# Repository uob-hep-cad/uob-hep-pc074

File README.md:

# Simple Charge Sensitive Amplifier with Integrated Shaping Amplifier

1000 electrons --> 8mV at output of shaper . i.e. ~ 50V/pC

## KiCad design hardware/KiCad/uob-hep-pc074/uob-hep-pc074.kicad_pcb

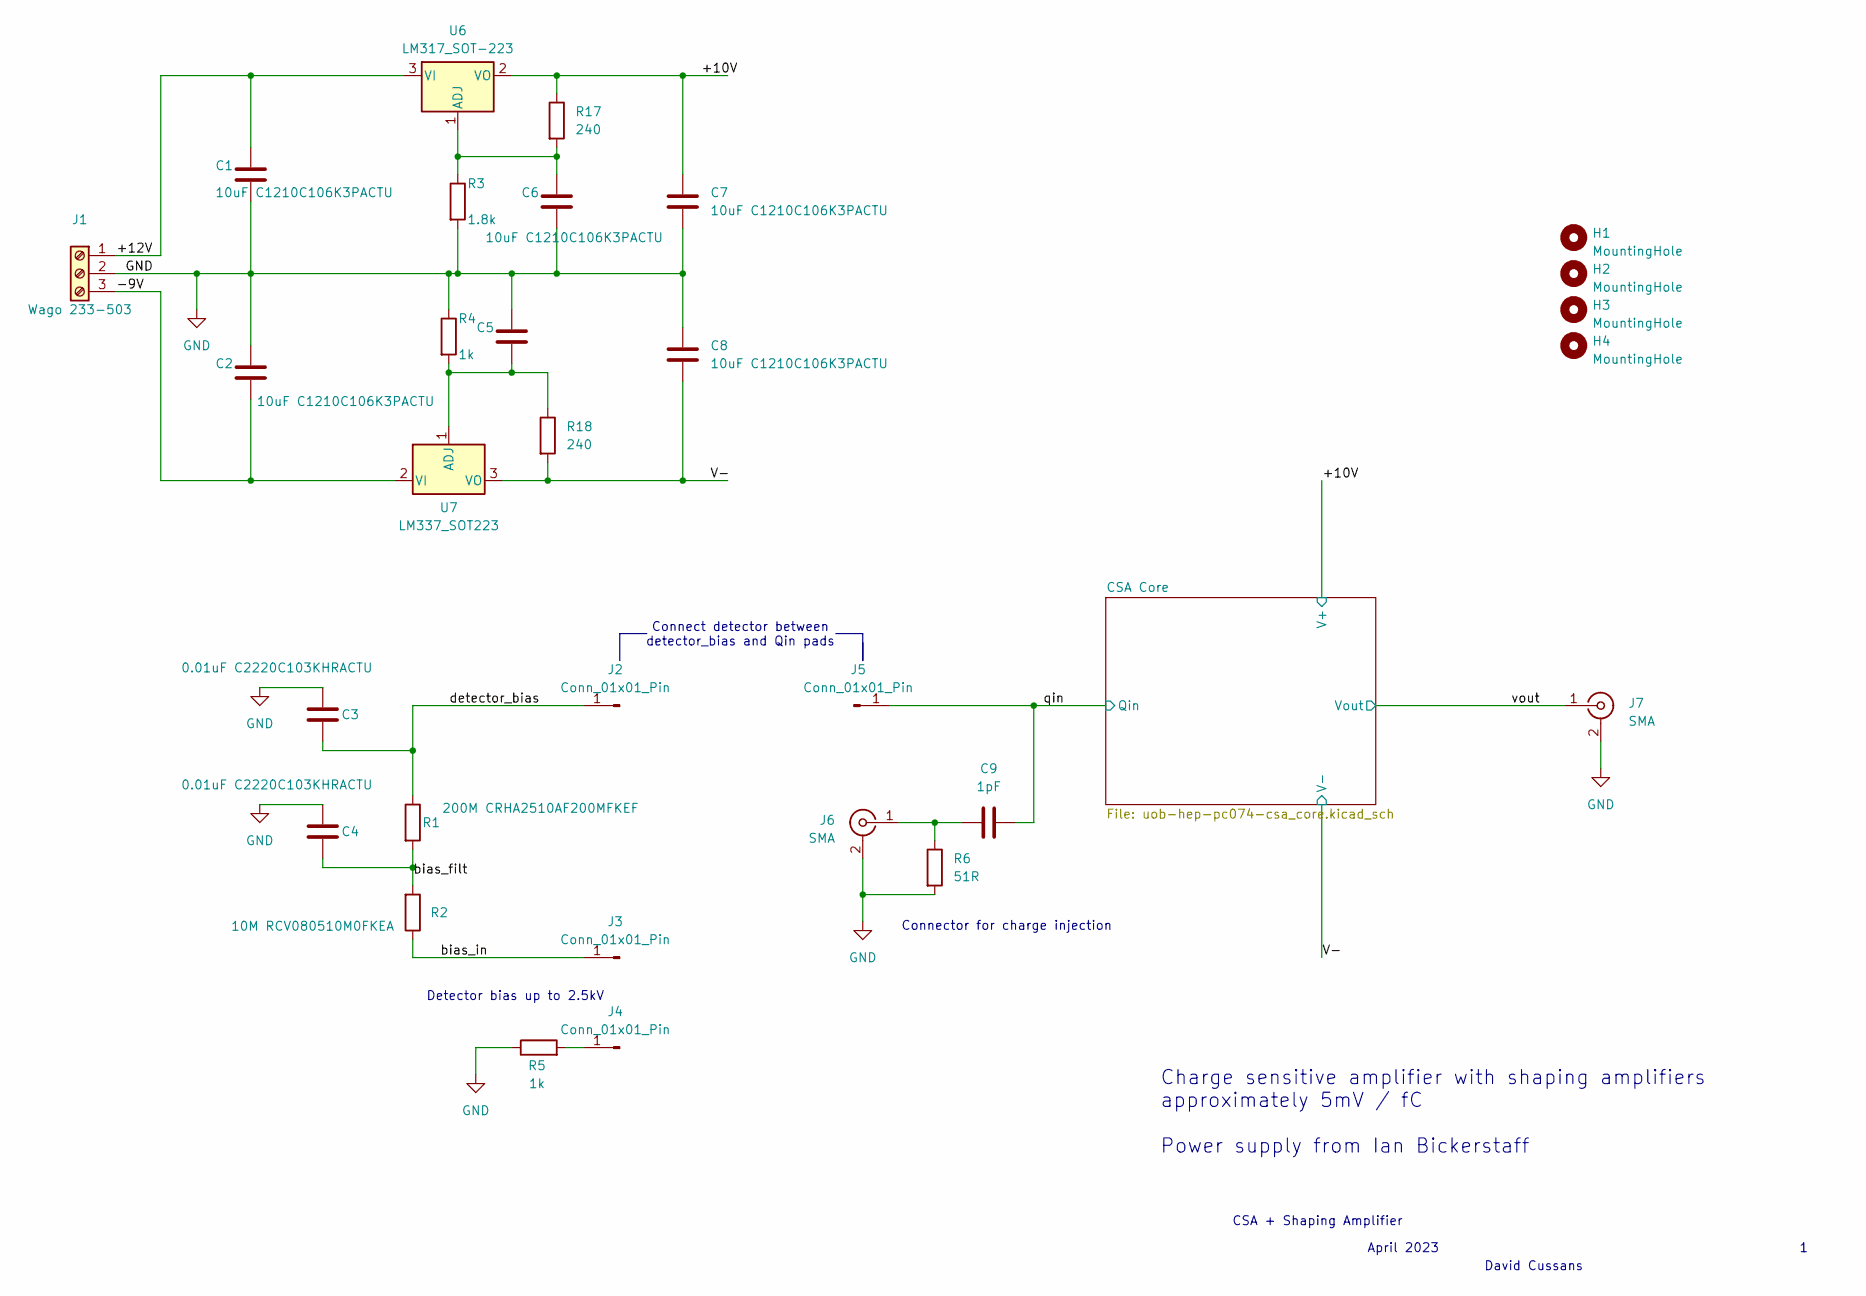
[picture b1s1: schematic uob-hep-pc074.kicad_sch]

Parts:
C1, C2, C5, C6, C7, C8: 10uF C1210C106K3PACTU; C_1210_3225Metric
C3, C4: 0.01uF C2220C103KHRACTU; C_2220_5750Metric_Pad1.97x5.40mm_HandSolder
C9: 1pF; C_0603_1608Metric_Pad1.08x0.95mm_HandSolder
H1, H2, H3, H4: MountingHole; MountingHole_2.7mm_M2.5
J1: Wago 233-503; TerminalBlock_WAGO_233-503_1x03_P2.54mm_45Degree
J2, J3, J4, J5: Conn_01x01_Pin; SolderWire-2sqmm_1x01_D2mm_OD3.9mm
J6, J7: SMA; SMA_Amphenol_901-144_Vertical
R1: 200M CRHA2510AF200MFKEF; R_2512_6332Metric_Pad1.40x3.35mm_HandSolder
R2: 10M RCV080510M0FKEA; R_0805_2012Metric
R3: 1.8k; R_0603_1608Metric_Pad0.98x0.95mm_HandSolder
R4, R5: 1k; R_0603_1608Metric_Pad0.98x0.95mm_HandSolder
R6: 51R; R_0603_1608Metric_Pad0.98x0.95mm_HandSolder
R17, R18: 240; R_0603_1608Metric_Pad0.98x0.95mm_HandSolder
U6: LM317_SOT-223; SOT-223-3_TabPin2
U7: LM337_SOT223; SOT-223-3_TabPin2

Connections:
/+10V: C7.1, R17.1, U6.2 (VO); also elsewhere on the board
/+12V: C1.1, J1.1, U6.3 (VI)
/-9V: C2.2, J1.3, U7.2 (VI)
/V-: C8.2, R18.2, U7.3 (VO); also elsewhere on the board
/bias_filt: C4.1, R1.2, R2.2
/bias_in: J3.1, R2.1
/detector_bias: C3.1, J2.1, R1.1
/qin: C9.2, J5.1; also elsewhere on the board
/vout: J7.1 (In); also elsewhere on the board
GND: C1.2, C2.1, C3.2, C4.2, C5.1, C6.2, C7.2, C8.1, J1.2, J6.2 (Ext), J7.2 (Ext), R3.2, R4.1, R5.1, R6.2; also elsewhere on the board
unnamed: J4.1, R5.2
unnamed: C9.1, J6.1 (In), R6.1
unnamed: C6.1, R3.1, R17.2, U6.1 (ADJ)
unnamed: C5.2, R4.2, R18.1, U7.1 (ADJ)

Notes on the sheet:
CSA + Shaping Amplifier
David Cussans
Connector for charge injection
Detector bias up to 2.5kV
Charge sensitive amplifier with shaping amplifiers approximately 5mV / fC Power supply from Ian Bickerstaff
Connect detector between detector_bias and Qin pads
April 2023

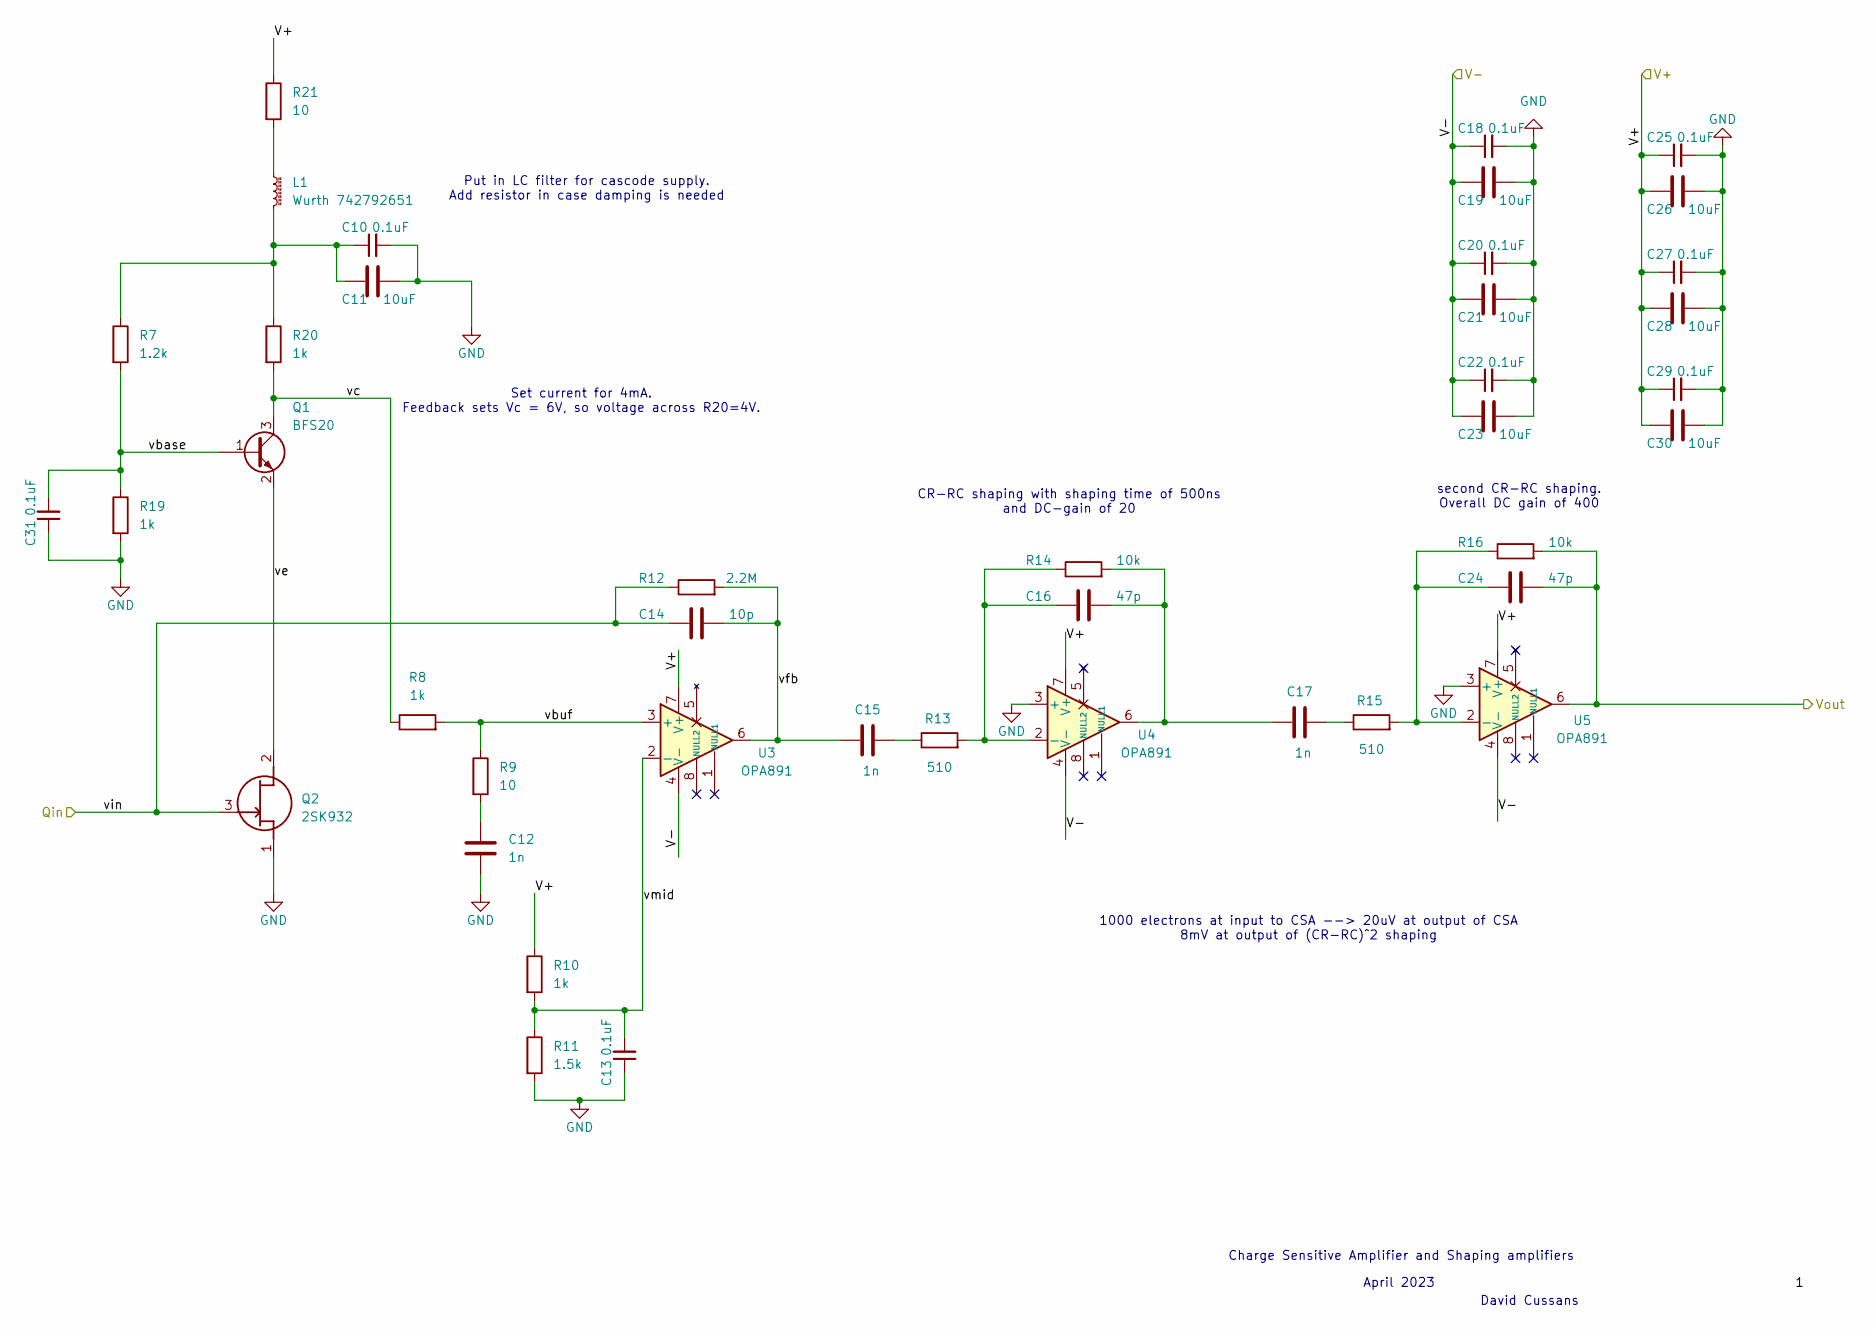
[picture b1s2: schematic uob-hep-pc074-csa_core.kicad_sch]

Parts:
C10, C13, C18, C20, C22, C25, C27, C29, C31: 0.1uF; C_0805_2012Metric
C11, C19, C21, C23, C26, C28, C30: 10uF; C_0805_2012Metric
C12: 1n; C_0603_1608Metric_Pad1.08x0.95mm_HandSolder
C14: 10p; R_0603_1608Metric_Pad0.98x0.95mm_HandSolder
C15, C17: 1n; R_0603_1608Metric_Pad0.98x0.95mm_HandSolder
C16, C24: 47p; R_0603_1608Metric_Pad0.98x0.95mm_HandSolder
L1: Wurth 742792651; L_0603_1608Metric_Pad1.05x0.95mm_HandSolder
Q1: BFS20; SOT-23
Q2: 2SK932; SOT-23; Manufacturer_Part_Number 2SK932
R7: 1.2k; R_0603_1608Metric_Pad0.98x0.95mm_HandSolder
R8, R10, R19, R20: 1k; R_0603_1608Metric_Pad0.98x0.95mm_HandSolder
R9, R21: 10; R_0603_1608Metric_Pad0.98x0.95mm_HandSolder
R11: 1.5k; R_0603_1608Metric_Pad0.98x0.95mm_HandSolder
R12: 2.2M; R_0603_1608Metric_Pad0.98x0.95mm_HandSolder
R13, R15: 510; R_0603_1608Metric_Pad0.98x0.95mm_HandSolder
R14, R16: 10k; R_0603_1608Metric_Pad0.98x0.95mm_HandSolder
U3, U4, U5: OPA891; SOIC-8_5.275x5.275mm_P1.27mm

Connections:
/+10V: C25.1, C26.1, C27.1, C28.1, C29.1, C30.1, R10.1, R21.1, U3.7 (V+), U4.7 (V+), U5.7 (V+); also elsewhere on the board
/CSA Core/vbase: C31.2, Q1.1 (B), R7.2, R19.1
/CSA Core/vbuf: R8.2, R9.1, U3.3 (+)
/CSA Core/vc: Q1.3 (C), R8.1, R20.2
/CSA Core/ve: Q1.2 (E), Q2.2 (D)
/CSA Core/vfb: C14.2, C15.1, R12.2, U3.6
/CSA Core/vmid: C13.2, R10.2, R11.1, U3.2 (-)
/V-: C18.1, C19.1, C20.1, C21.1, C22.1, C23.1, U3.4 (V-), U4.4 (V-), U5.4 (V-); also elsewhere on the board
/qin: C14.1, Q2.3 (G), R12.1; also elsewhere on the board
/vout: C24.2, R16.2, U5.6; also elsewhere on the board
GND: C10.2, C11.2, C12.2, C13.1, C18.2, C19.2, C20.2, C21.2, C22.2, C23.2, C25.2, C26.2, C27.2, C28.2, C29.2, C30.2, C31.1, Q2.1 (S), R11.2, R19.2, U4.3 (+), U5.3 (+); also elsewhere on the board
unnamed: C10.1, C11.1, L1.2, R7.1, R20.1
unnamed: C12.1, R9.2
unnamed: C15.2, R13.1
unnamed: C16.2, C17.1, R14.2, U4.6
unnamed: C17.2, R15.1
unnamed: L1.1, R21.2
unnamed: C16.1, R13.2, R14.1, U4.2 (-)
unnamed: C24.1, R15.2, R16.1, U5.2 (-)

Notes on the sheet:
CR-RC shaping with shaping time of 500ns and DC-gain of 20
Charge Sensitive Amplifier and Shaping amplifiers
David Cussans
second CR-RC shaping. Overall DC gain of 400
1000 electrons at input to CSA --> 20uV at output of CSA 8mV at output of (CR-RC)^2 shaping
Set current for 4mA. Feedback sets Vc = 6V, so voltage across R20=4V.
Put in LC filter for cascode supply. Add resistor in case damping is needed
April 2023

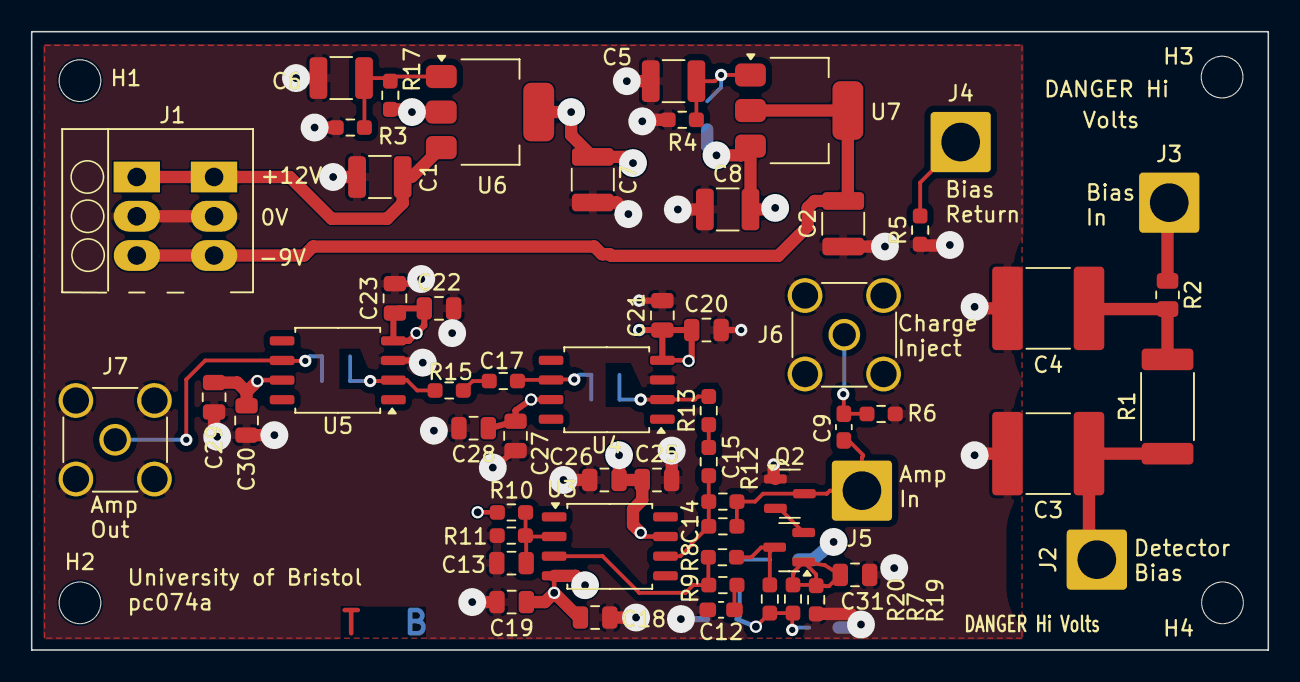
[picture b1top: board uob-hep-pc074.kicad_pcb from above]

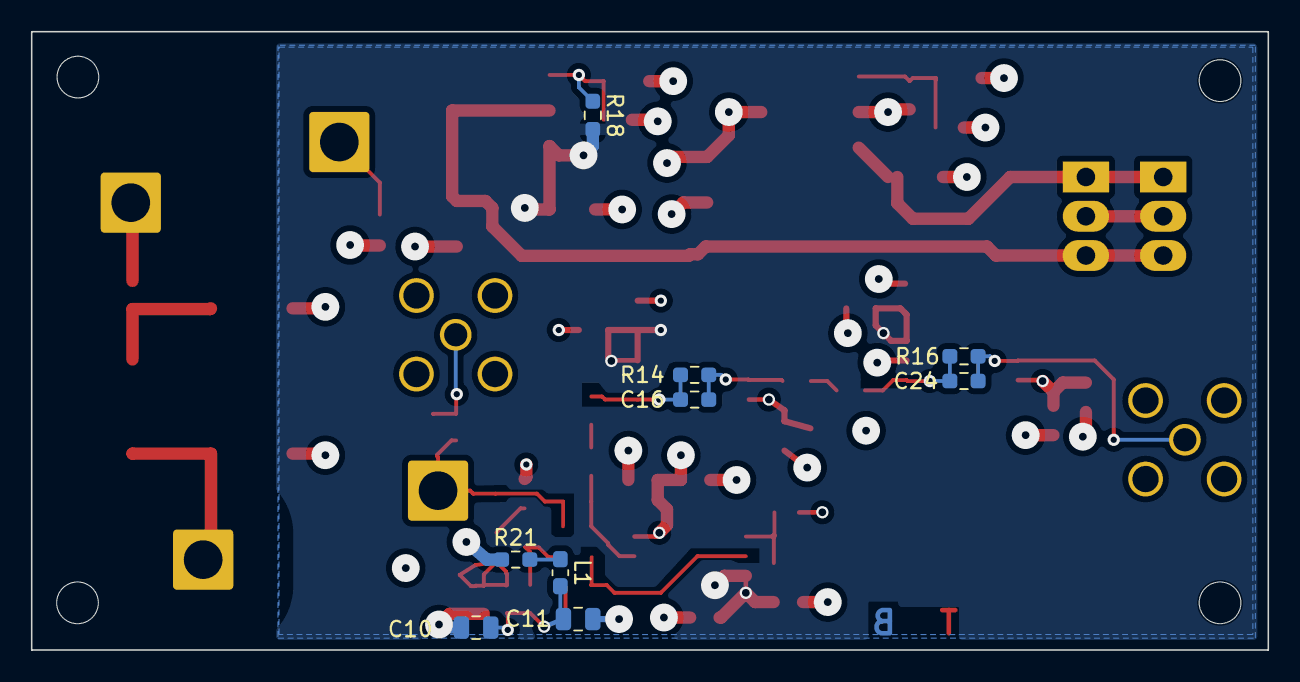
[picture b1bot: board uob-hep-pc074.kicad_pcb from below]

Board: 4 copper layers, 80.0 x 40.0 mm, 71 parts (9 on the bottom side), 28 nets.

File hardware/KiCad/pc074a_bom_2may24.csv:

Reference,Value,Datasheet,Footprint,,Qty,DNP,
"C1,C2,C5,C6,C7,C8",10uF   C1210C106K3PACTU,~,Capacitor_SMD:C_1210_3225Metric,RS 173-4070,6,,
"C3,C4",0.01uF  C2220C103KHRACTU,~,Capacitor_SMD:C_2220_5750Metric_Pad1.97x5.40mm_HandSolder,RS     723-6972,2,,"Substitute Murata 10nF MLCC, 2kV dc V, ±10%

RS Stock No.:
    723-6972
Mfr. Part No.: GR455DR73D103KW01L"
C9,1pF,~,Capacitor_SMD:C_0603_1608Metric_Pad1.08x0.95mm_HandSolder,RS 788-0345,1,,
"C10,C13,C18,C20,C22,C25,C27,C29,C31",0.1uF,~,Capacitor_SMD:C_0805_2012Metric,RS      264-4416,9,,
"C11,C19,C21,C23,C26,C28,C30",10uF,~,Capacitor_SMD:C_0805_2012Metric,RS     915-9328,7,,
"C12,C15,C17",1n,~,Capacitor_SMD:R_0603_1608Metric_Pad0.98x0.95mm_HandSolder,RS 272-7830,3,,
C14,10p,~,Resistor_SMD:R_0603_1608Metric_Pad0.98x0.95mm_HandSolder,  RS   272-7818P,1,,
"C16,C24",47p,~,Resistor_SMD:R_0603_1608Metric_Pad0.98x0.95mm_HandSolder,RS     264-4517,2,,
"H1,H2,H3,H4",MountingHole,~,MountingHole:MountingHole_2.7mm_M2.5,,4,DNP,
J1,Wago 233-503,~,UoB Cremat Library:TerminalBlock_WAGO_233-503_1x03_P2.54mm_45Degree,RS 181-4642,1,,
"J2,J3,J4,J5",Conn_01x01_Pin,~,Connector_Wire:SolderWire-2sqmm_1x01_D2mm_OD3.9mm,,4,DNP,
"J6,J7",SMA, ~,Connector_Coaxial:SMA_Amphenol_901-144_Vertical,RS     144-0894,2,,
L1,Wurth 742792651,~,Inductor_SMD:L_0603_1608Metric_Pad1.05x0.95mm_HandSolder,RS 124-1835,1,,
Q1,BFS20,https://www.onsemi.com/pub/Collateral/BC818-D.pdf,Package_TO_SOT_SMD:SOT-23,RS     153-2886P,1,,
Q2,2SK932,https://www.onsemi.com/download/data-sheet/pdf/2sk932-d.pdf,Package_TO_SOT_SMD:SOT-23,RS     792-5173,1,,
R1,200M   CRHA2510AF200MFKEF,~,Resistor_SMD:R_2512_6332Metric_Pad1.40x3.35mm_HandSolder,RS 211-9408,1,,
R2,10M  RCV080510M0FKEA,~,Resistor_SMD:R_0805_2012Metric,RS     905-9802,1,,
R3,1.8k,~,Resistor_SMD:R_0603_1608Metric_Pad0.98x0.95mm_HandSolder,RS     678-9926,1,,
"R4,R5,R8,R10,R19,R20",1k,~,Resistor_SMD:R_0603_1608Metric_Pad0.98x0.95mm_HandSolder,RS     243-0589,6,,
R6,51R,~,Resistor_SMD:R_0603_1608Metric_Pad0.98x0.95mm_HandSolder,RS     262-9901,1,,
R7,1.2k,~,Resistor_SMD:R_0603_1608Metric_Pad0.98x0.95mm_HandSolder,RS     678-9888,1,,
"R9,R21",10,~,Resistor_SMD:R_0603_1608Metric_Pad0.98x0.95mm_HandSolder,RS     243-0573,2,,
R11,1.5k,~,Resistor_SMD:R_0603_1608Metric_Pad0.98x0.95mm_HandSolder,RS 678-9908,1,,
R12,2.2M,~,Resistor_SMD:R_0603_1608Metric_Pad0.98x0.95mm_HandSolder,RS     679-0162,1,,
"R13,R15",510,~,Resistor_SMD:R_0603_1608Metric_Pad0.98x0.95mm_HandSolder,RS 679-0504,2,,
"R14,R16",10k,~,Resistor_SMD:R_0603_1608Metric_Pad0.98x0.95mm_HandSolder,RS     243-0480,2,,
"R17,R18",240,~,Resistor_SMD:R_0603_1608Metric_Pad0.98x0.95mm_HandSolder,RS     679-0021,2,,
"U3,U4,U5",OPA891,https://www.analog.com/media/en/technical-documentation/data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,Package_SO:SOIC-8_5.275x5.275mm_P1.27mm,356-8335P,3,,Substitute THS4031
U6,LM317_SOT-223,http://www.ti.com/lit/ds/symlink/lm317.pdf,Package_TO_SOT_SMD:SOT-223-3_TabPin2,    661-6128,1,,
U7,LM337_SOT223,http://www.ti.com/lit/ds/symlink/lm337-n.pdf,Package_TO_SOT_SMD:SOT-223-3_TabPin2,761-4612,1,,

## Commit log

2024-04-11 More schemataic tidying. Added a csa_core_simulation.kicad_pro to simulate CSA core. Tidied csa_core to make it simulatable, but needs work - OP analysis doesn't converge at the moment. (Need to fidd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
2024-04-29 Added lead-lag compenstation after JFET which seems to stabilize loop in simulation. Added CR-RC shaping/amplification. Committing changes before starting simulation of shapers
2024-04-29 End of day save. Just needs voids added to planes to reduce capacitance
2026-03-18 Trying to complete merge
2026-03-18 Produced gerbers
2026-03-18 Generated artwork
2026-03-18 Printed PDF schemaics. Saved schematic and PCB as KiCAD 9
2026-04-07 Copied UoB TICSP project to hardware/KiCAD/uob-hep-pc074
